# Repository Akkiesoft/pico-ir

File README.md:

# Pico IR-LED Module

Raspberry Pi Picoで使える赤外線学習モジュールのKiCad向け基板データです。この基板データの作り方、必要な部品などは、Raspberry JAM Tokyo 2024.2で発表したスライドで解説しています。詳しくは下記リンクを参照してください。

Rev.1（スライド発表時）には、赤外線受光モジュールの差し込みの表裏が逆になっているバグがあります。公開しているRev.2移行では修正およびシルク印刷で案内が追加されています。なお、指し間違えるとモジュールが壊れるので注意してください（指し間違えのケアは回路ではしていません、ごめんなさい）。

https://speakerdeck.com/akkiesoft/20240226-rpi-jam

https://akkiesoft.hatenablog.jp/entry/20240309/1709987763

## License

MIT License

2024 @Akkiesoft

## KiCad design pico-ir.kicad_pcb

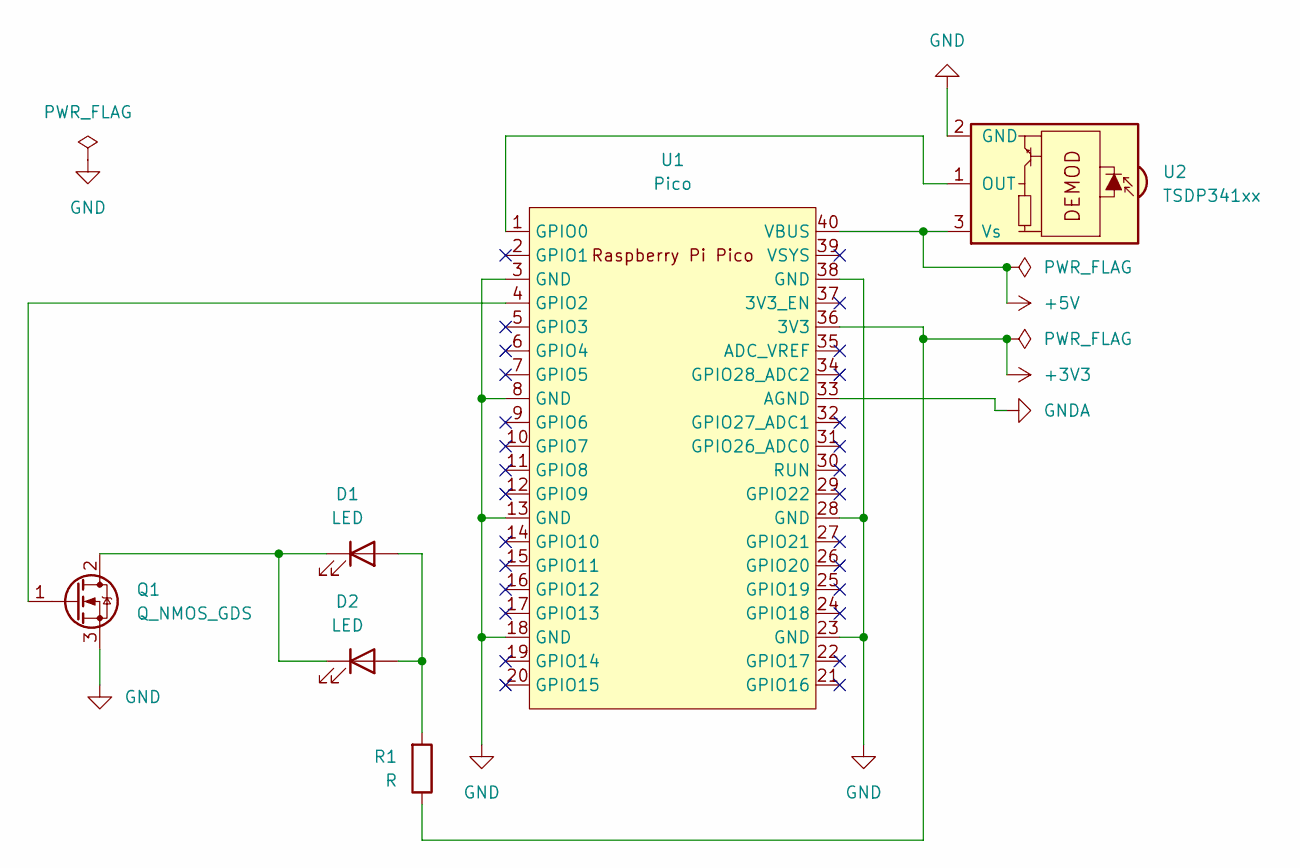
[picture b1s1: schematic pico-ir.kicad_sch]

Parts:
D1, D2: LED; PinSocket_1x02_P2.54mm_Horizontal
Q1: Q_NMOS_GDS; TO-251-3-1EP_Horizontal_TabDown
R1: R; R_Axial_DIN0207_L6.3mm_D2.5mm_P7.62mm_Horizontal
U1: Pico; RPi_Pico_SMD_TH
U2: TSDP341xx; PinSocket_1x03_P2.54mm_Horizontal

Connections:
+3V3: R1.1, U1.36 (3V3)
+5V: U1.40 (VBUS), U2.3 (Vs)
GND: Q1.3 (S), U1.3 (GND), U1.8 (GND), U1.13 (GND), U1.18 (GND), U1.23 (GND), U1.28 (GND), U1.38 (GND), U2.2 (GND)
GNDA: U1.33 (AGND)
unnamed: D1.2 (A), D2.2 (A), R1.2
unnamed: D1.1 (K), D2.1 (K), Q1.2 (D)
unnamed: Q1.1 (G), U1.4 (GPIO2)
unnamed: U1.1 (GPIO0), U2.1 (OUT)

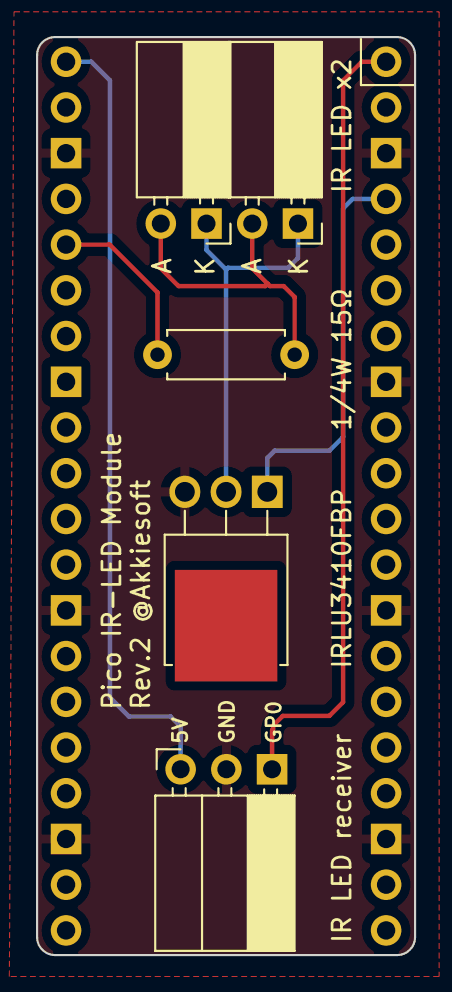
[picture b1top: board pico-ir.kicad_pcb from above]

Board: 2 copper layers, 21.0 x 51.0 mm, 6 parts (1 on the bottom side), 7 nets.

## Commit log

2024-12-06 init
